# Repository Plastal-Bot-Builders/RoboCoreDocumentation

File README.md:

# RoboCore

RoboCore is a classroom robot kit and coding platform, designed and built in Zambia by **Plastal-Bot Builders** (Lusaka). It has four parts:
- an **ESP32-S3 controller board**;
- a **3D-printed robot** with a parallel lift and a geared gripper;
- a **retail box** with a quick-start guide;
- the **RoboCore IDE**, where students code the robot with blocks or C++.

This repository holds the design sources for all of it: the PCBs, the mechanical design, the software design and the brand. Pitch decks, grant applications and community posts live elsewhere.

<table>
  <tr>
    <td width="50%"></td>
    <td width="50%"></td>
  </tr>
  <tr>
    <td align="center"><b>The robot</b> (V2, Fusion 360)</td>
    <td align="center"><b>The controller board</b> (V2, KiCad 9)</td>
  </tr>
</table>

---

## The controller board (V2)

An XRP-style robot controller on a 68 × 60 mm, 4-layer board. Everything a classroom robot needs is on one board, and it charges and programs over one USB-C cable.

| | |
|---|---|
| **Brain** | ESP32-S3-WROOM-1-N8R2: dual core, Wi-Fi and Bluetooth LE, 8 MB flash, 2 MB PSRAM. Programs over native USB, so no separate programmer is needed |
| **Motors** | 2 DC motors with encoders (DRV8411A dual H-bridge, limited to 1.0 A per motor). JST SH 6-pin, matching the SparkFun XRP motors |
| **Servos** | 4 servo ports on a 5.5 V supply (TPS61089 boost, about 2.5–3 A continuous) |
| **Sensors** | Ultrasonic port (4-pin), 3-channel line-sensor port (5-pin, analog), Qwiic I2C, and an LSM6DSOX 6-axis motion sensor on board |
| **Power** | One Li-ion cell, or several in parallel (3.0–4.2 V), on an XT30 plug. Protected against a reversed or over-voltage pack. USB-C charging at 1 A (MCP73871) and a steady 3.3 V from a buck-boost converter |
| **On board** | RGB LED, buzzer, RESET, BOOT and USER buttons, charge and power LEDs, two 14-pin expansion headers |

<table>
  <tr>
    <td width="50%"></td>
    <td width="50%"></td>
  </tr>
  <tr>
    <td align="center">Top: every port labelled on the silkscreen</td>
    <td align="center">Underside: pin names and the "Designed in Zambia" artwork</td>
  </tr>
  <tr>
    <td></td>
    <td></td>
  </tr>
  <tr>
    <td align="center">The ESP32-S3 module, buttons and IMU</td>
    <td align="center">The connector edge: ultrasonic, battery, USB-C, line sensor, power switch</td>
  </tr>
</table>

- **Design files:** `hardware/controller_v2/`. Open `RoboCore_V2.kicad_pro` in KiCad 9.
- **Renders:** studio renders made in Blender are in `hardware/controller_v2/renders/`, full size and 1600 px, with transparent and white backgrounds. Each shot has a map of where every part sits in the image, for pinouts and highlights in the IDE or on the website. See [its README](hardware/controller_v2/renders/README.md).
- **Before connecting anything:** the sensor headers are not keyed, so a cable can go on backwards. Read [the wrong-plug check](docs/RoboCore_V2_wrong_plug_check.md). Known issues and bring-up findings are kept in [the errata list](docs/RoboCore_V2_errata.md).
- **Sensor boards:** our own 3-channel line sensor and ultrasonic boards are designed in `hardware/sensors/`. For now the robot uses bought-in modules.

## The robot

The current robot (V3, the V-wheel version): an open printed frame with Warren-truss sides, two encoder motors with 56 mm wheels, four V-wheels in wheel wells, a parallel four-bar lift on one MG90S servo (the gripper stays level from the floor to +40 degrees) and a geared gripper on a second servo. The RoboCore V2 controller sits between the side frames, three 18650 cells lie in a printed cradle, the sonar sits in a housing at the front, and a cream rear deck carries an 8 mm Technic/M4 hole grid. 154 x 286 x 111 mm with the lift level, about 620 g; every part prints flat without supports. The V3 model lives in Fusion 360 (document "RoboCore V3 Robot"); the files below are the earlier V2 robot, kept for reference.

- **Model:** `mechanical/robot_v2/RoboCore_V2_Robot.f3d` (Fusion 360) and `.step` (any CAD program).
- **Generator:** the model is built by a Python generator through the Fusion API (`mechanical/robot_v2/fusion/`). [Its README](mechanical/robot_v2/README.md) explains the parameters, the fasteners and the checks: clashes, overhangs, antenna clearance and caster load.
- **Print files:** `mechanical/robot_v2/print/`, already in print orientation. Every part prints without supports on a 180 mm bed.
- **Cardboard version:** a low-cost cardboard chassis template is in `mechanical/robot_v2/cardboard/`.

## The box

<table>
  <tr>
    <td width="50%"></td>
    <td width="50%"></td>
  </tr>
</table>

A printed mailer box, XRP-style, with the quick-start guide printed inside the lid and an insert with a pocket traced from the robot (lift lowered, jaws on the floor) plus a strip for the cable, screws and card. Outer 303 x 213 x 91 mm. The print-ready 1:1 PDFs are in `mechanical/robot_v2/packaging/out_v3/` (generator `make_box_v3.py`; the V2 box is in `out/`).

## Software

- **RoboCore IDE design** (`software/ide_design/`): the screens of the RoboCore IDE, built in Figma by a plugin. It covers block coding (Google Blockly) and C++ (Monaco), a hardware-first block catalogue, and a behaviour spec. The app itself is developed in its own repository, [robocore-ide](https://github.com/Plastal-Bot-Builders/robocore-ide).
- **System architecture** (`software/architecture/`): UML and C4 diagrams of the whole platform, also generated into Figma.
- **Firmware** (`software/firmware/motion/`): an arm-aware braking limiter in C, with tests.

## Brand

<table>
  <tr>
    <td width="33%"></td>
    <td width="33%"></td>
    <td width="33%"></td>
  </tr>
</table>

Event branding is in `design/event_branding/`: roll-up, pop-up, banner, A5 flyer, A4 tri-fold and the brand kit, built in Figma by a plugin. The topographic backgrounds are drawn from Copperbelt elevation data.

---

## Repository layout

```
hardware/          PCB design (KiCad 9)
  controller_v2/     RoboCore V2 controller: project files, libraries (lib/), PCBWay and JLCPCB order
                     packages (fab/), generator, check, costing and Blender render scripts (tools/),
                     silkscreen artwork sources (technicalreference/), studio renders (renders/)
  sensors/           Line sensor (3-channel) and ultrasonic carrier boards for V2
  controller_v1/     RoboCore V1 (ESP32-C3) controller with its fab package and review scripts
  libraries/         Shared symbol and footprint libraries used by V1
  datasheets/        Component datasheets
mechanical/        Mechanical design
  robot_v2/          The Fusion 360 robot: model, Python generator (fusion/), print files (print/),
                     component STEP exports (export/), mailer box (packaging/), cardboard version
                     (cardboard/), vendor models (vendor/), renders
  board_step/        STEP models of the boards, for mechanical integration
  reference/         Motor and XRP reference pictures and models
  chassis_v1_spec/   Specification and script of the V1 chassis
software/          Software
  ide_design/        RoboCore IDE screens (Figma plugin), app icon, block catalogue, behaviour spec
  architecture/      UML + C4 system architecture (Figma plugin)
  firmware/motion/   Arm-aware braking limiter (C, with tests)
design/            Brand
  event_branding/    Roll-up, banner, flyer, tri-fold and brand kit (Figma plugin), topographic maps
docs/              Specification, costing and sourcing, component lists and supplier quote requests,
                   wrong-plug check and errata, schematic PDFs, part photos, A4 technical-reference
                   posters, progress renders, hand-off notes, PCBWay sponsorship request
tools/             sync_from_sources.sh: copies the working sources into this repo
```

## Opening the designs

- **PCB:** open `hardware/controller_v2/RoboCore_V2.kicad_pro` in KiCad 9. Project libraries resolve through `${KIPRJMOD}/lib`; the V1 project's symbol table points at `../libraries`.
- **Robot:** `mechanical/robot_v2/RoboCore_V2_Robot.f3d` opens in Fusion 360; the STEP beside it opens anywhere.
- **Box:** `mechanical/robot_v2/packaging/README.md`. The print files are 1:1 PDFs.
- **Board renders:** `hardware/controller_v2/tools/blender/render_board.sh` re-renders them in Blender 5.1, from the KiCad model.
- **Figma plugins:** the READMEs in `software/ide_design/`, `software/architecture/` and `design/event_branding/` explain how to load and run each plugin.

## Status (2026-10-23)

- **Controller V2:** two assembled prototypes are paid for at PCBWay (order YU1827457, 14 October) and expected to ship around 11 November. Bring-up findings will go into [the errata list](docs/RoboCore_V2_errata.md).
- **Robot:** rev 6. The model and STEP here are Fusion v33.
- **Sensor boards:** designed, not yet ordered. The robot uses bought-in modules for now.
- **IDE:** in development in [robocore-ide](https://github.com/Plastal-Bot-Builders/robocore-ide).
- **Parts:** the component list and supplier quote request for two robots are in `docs/`.

## Keeping this repo up to date

The design work happens in working folders outside this repo. Copy it in, then commit:

```bash
tools/sync_from_sources.sh           # list what changed
tools/sync_from_sources.sh --apply   # copy it in
```

The script lists every source folder it copies. On a slow connection, push large changes in several small commits.

## Licence

MIT, see `LICENSE`. Vendor models under `mechanical/robot_v2/vendor/` keep their own licences, noted in each folder's `SOURCE.txt`.

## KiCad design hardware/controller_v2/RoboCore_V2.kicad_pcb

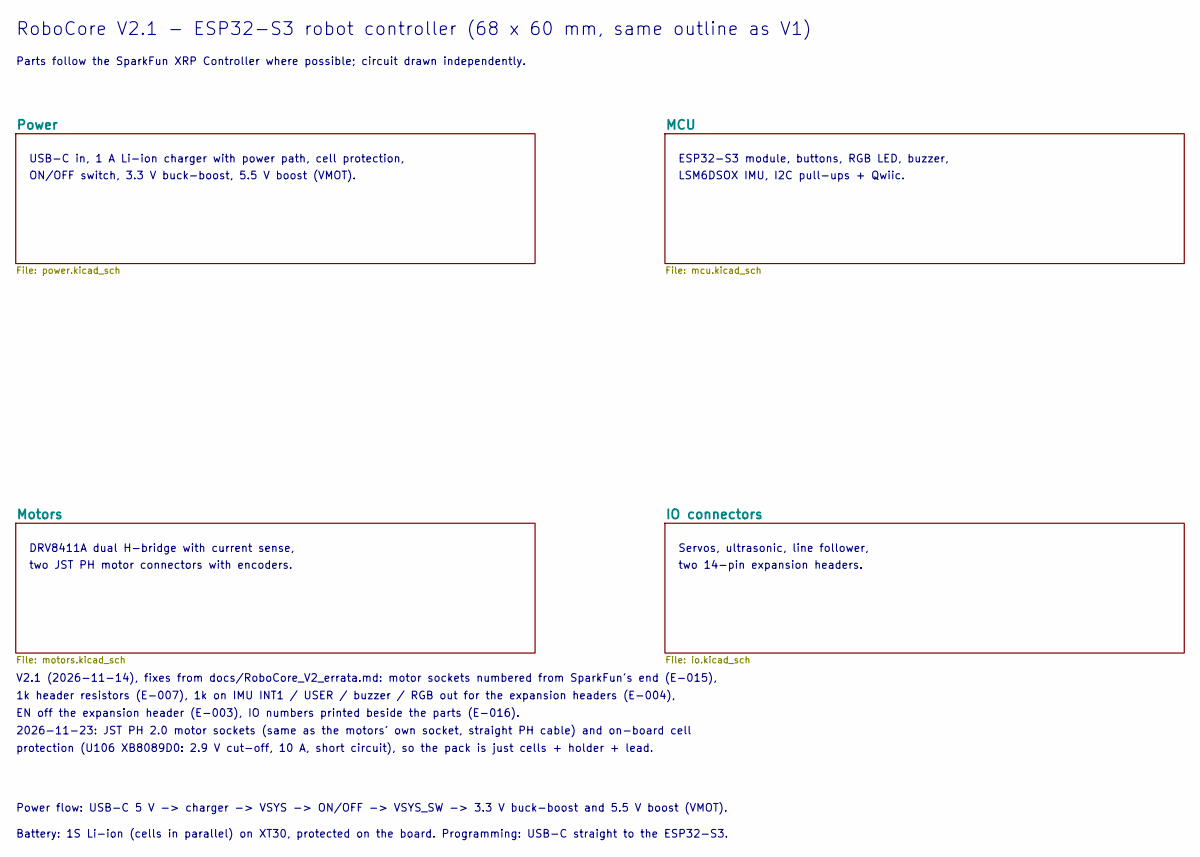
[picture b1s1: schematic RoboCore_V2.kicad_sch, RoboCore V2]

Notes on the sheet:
USB-C in, 1 A Li-ion charger with power path, cell protection,
ON/OFF switch, 3.3 V buck-boost, 5.5 V boost (VMOT).
ESP32-S3 module, buttons, RGB LED, buzzer,
LSM6DSOX IMU, I2C pull-ups + Qwiic.
DRV8411A dual H-bridge with current sense,
two JST PH motor connectors with encoders.
Servos, ultrasonic, line follower,
two 14-pin expansion headers.
RoboCore V2.1 - ESP32-S3 robot controller (68 x 60 mm, same outline as V1)
V2.1 (2026-11-14), fixes from docs/RoboCore_V2_errata.md: motor sockets numbered from SparkFun's end (E-015),
1k header resistors (E-007), 1k on IMU INT1 / USER / buzzer / RGB out for the expansion headers (E-004),
EN off the expansion header (E-003), IO numbers printed beside the parts (E-016).
2026-11-23: JST PH 2.0 motor sockets (same as the motors' own socket, straight PH cable) and on-board cell
protection (U106 XB8089D0: 2.9 V cut-off, 10 A, short circuit), so the pack is just cells + holder + lead.
Parts follow the SparkFun XRP Controller where possible; circuit drawn independently.
Power flow: USB-C 5 V -> charger -> VSYS -> ON/OFF -> VSYS_SW -> 3.3 V buck-boost and 5.5 V boost (VMOT).
Battery: 1S Li-ion (cells in parallel) on XT30, protected on the board. Programming: USB-C straight to the ESP32-S3.

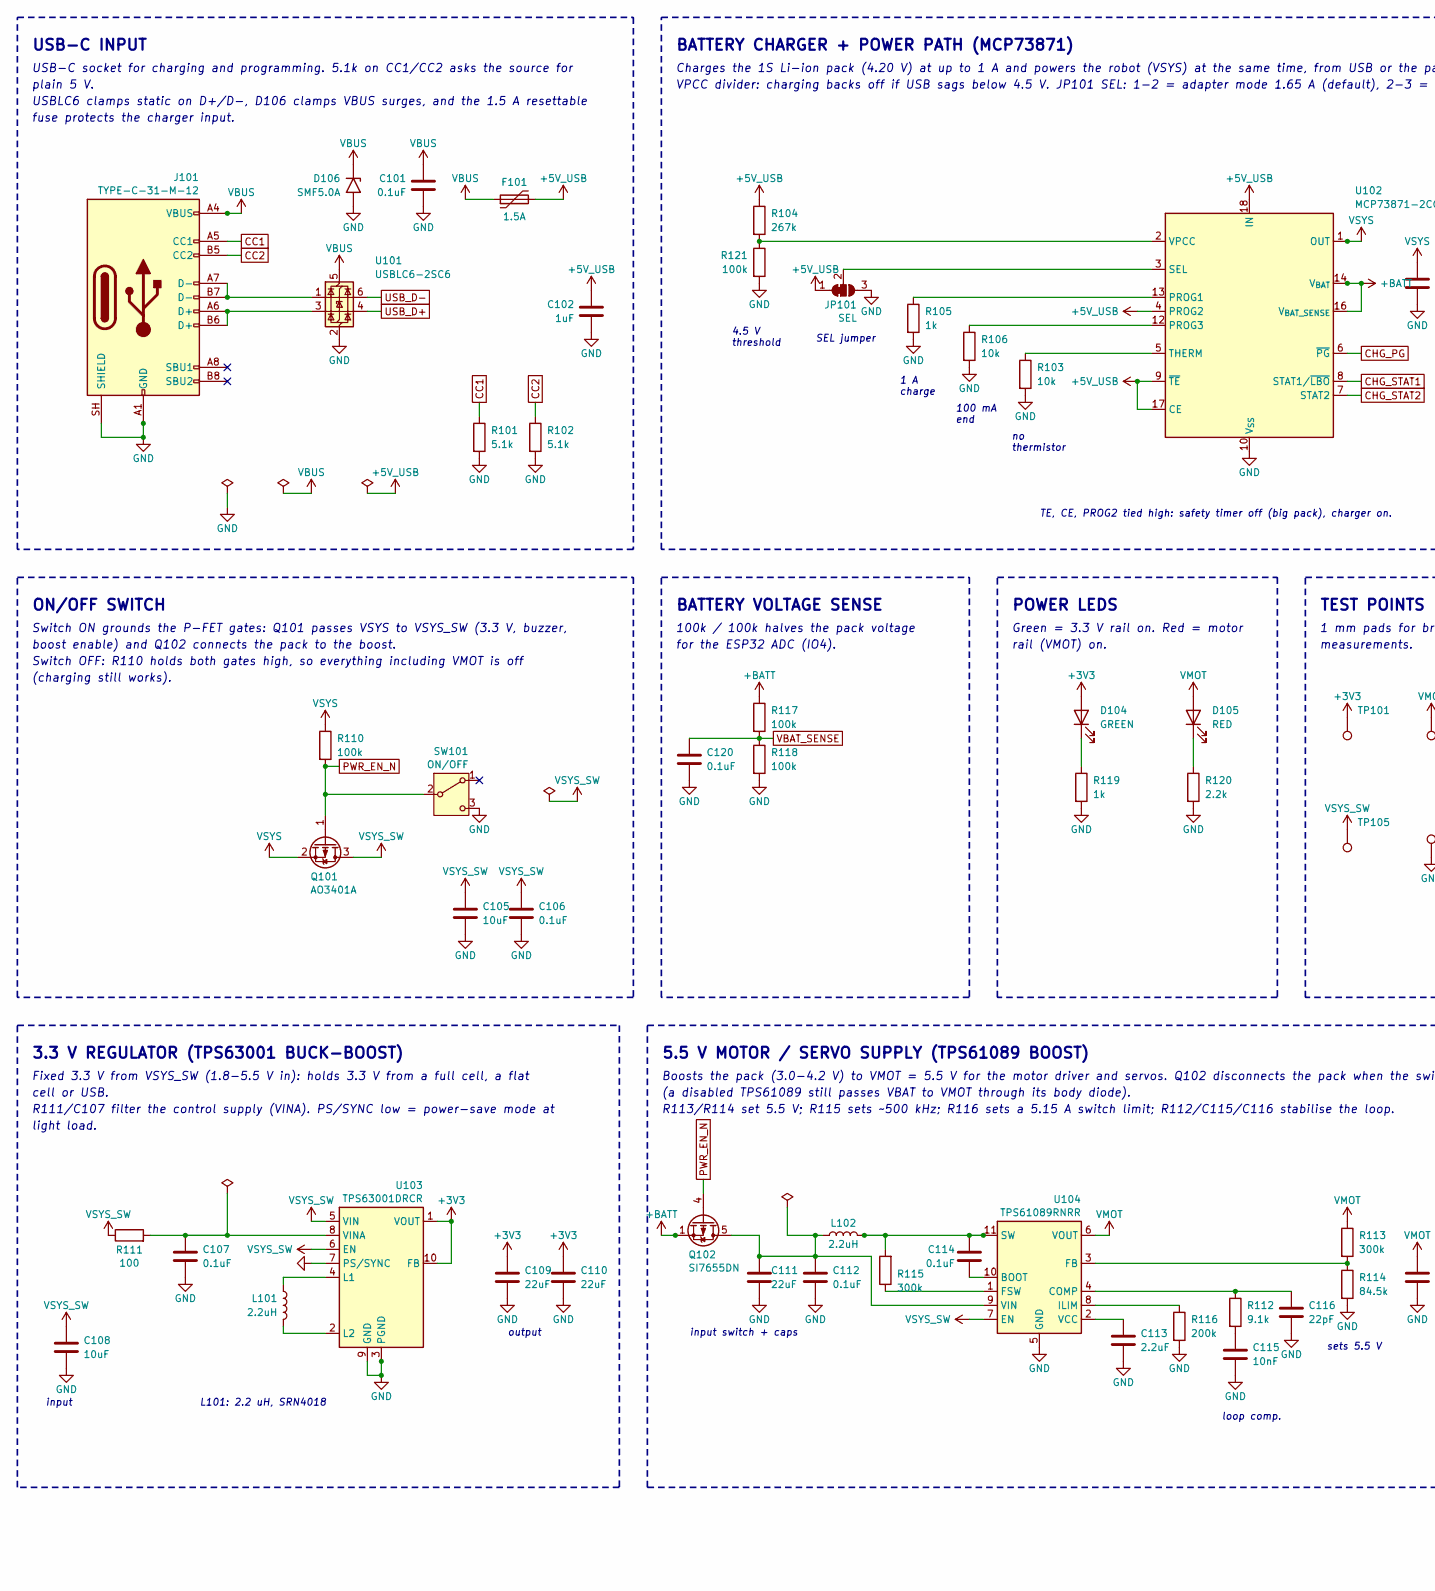
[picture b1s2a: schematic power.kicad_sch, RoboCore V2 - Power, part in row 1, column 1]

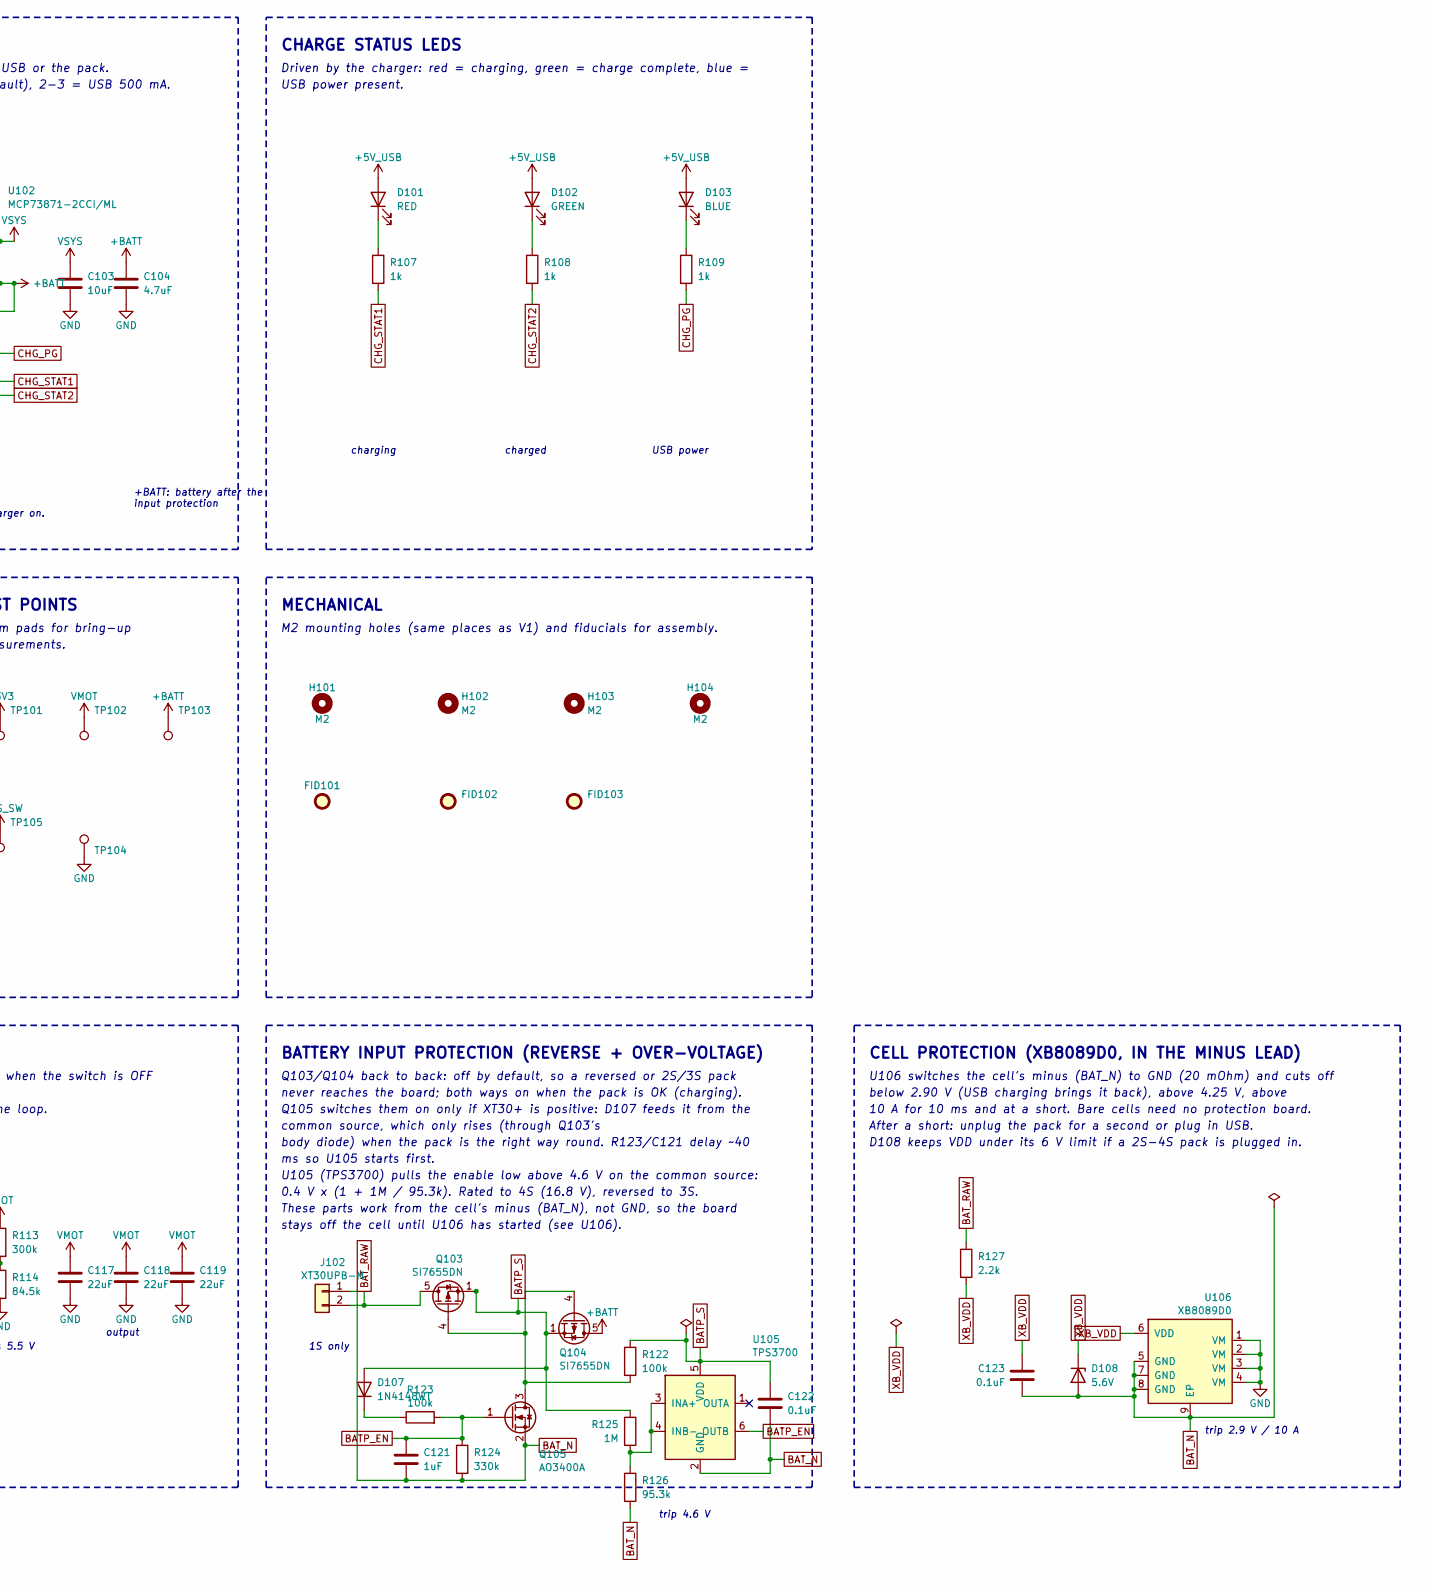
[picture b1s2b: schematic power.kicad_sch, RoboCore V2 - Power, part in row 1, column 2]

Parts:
C101, C106, C107, C112, C114, C120, C122, C123: 0.1uF; C_0402_1005Metric; LCSC C960916
C102: 1uF; C_0603_1608Metric; LCSC C5673
C103: 10uF; C_0603_1608Metric; LCSC C92487
C104: 4.7uF; C_0805_2012Metric; LCSC C1779
C105, C108: 10uF; C_0805_2012Metric; LCSC C1713
C109, C110: 22uF; C_0805_2012Metric; LCSC C45783
C111, C117, C118, C119: 22uF; C_1206_3216Metric; LCSC C12891
C113: 2.2uF; C_0603_1608Metric; LCSC C23630
C115: 10nF; C_0402_1005Metric; LCSC C15195
C116: 22pF; C_0402_1005Metric; LCSC C70464
C121: 1uF; C_0402_1005Metric; LCSC C16193167
D101, D105: RED; LED_0603_1608Metric; LCSC C125099
D102, D104: GREEN; LED_0603_1608Metric; LCSC C125098
D103: BLUE; LED_0603_1608Metric; LCSC C99290
D106: SMF5.0A; D_SMF; LCSC C151296
D107: 1N4148WT; D_SOD-523; LCSC C232841
D108: 5.6V; D_SOD-523; LCSC C516598
F101: 1.5A; Fuse_1812_4532Metric; LCSC C78695
FID101, FID102, FID103: Fiducial; Fiducial_1mm_Mask2mm
H101, H102, H103, H104: M2; MountingHole_2.2mm_M2
J101: TYPE-C-31-M-12; USB_C_Receptacle_HRO_TYPE-C-31-M-12; LCSC C165948
J102: XT30UPB-M; AMASS_XT30UPB-M_1x02_P5.0mm_Vertical; LCSC C428721
JP101: SEL; SolderJumper-3_P1.3mm_Bridged12_RoundedPad1.0x1.5mm
L101: 2.2uH; L_Bourns-SRN4018; LCSC C913207
L102: 2.2uH; L_Bourns_SRP5030CA; LCSC C2046809
Q101: AO3401A; SOT-23; LCSC C15127
Q102, Q103, Q104: SI7655DN; Vishay_PowerPAK_1212-8_Single; LCSC C727830
Q105: AO3400A; SOT-23; LCSC C20917
R101, R102: 5.1k; R_0402_1005Metric; LCSC C25905
R103, R106: 10k; R_0402_1005Metric; LCSC C25744
R104: 267k; R_0402_1005Metric; LCSC C270622
R105, R107, R108, R109, R119: 1k; R_0402_1005Metric; LCSC C106235
R110, R117, R118, R121, R122, R123: 100k; R_0402_1005Metric; LCSC C25741
R111: 100; R_0402_1005Metric; LCSC C106232
R112: 9.1k; R_0402_1005Metric; LCSC C25926
R113, R115: 300k; R_0402_1005Metric; LCSC C25774
R114: 84.5k; R_0402_1005Metric; LCSC C26988
R116: 200k; R_0402_1005Metric; LCSC C25764
R120, R127: 2.2k; R_0402_1005Metric; LCSC C25879
R124: 330k; R_0402_1005Metric; LCSC C25778
R125: 1M; R_0402_1005Metric; LCSC C26083
R126: 95.3k; R_0402_1005Metric; LCSC C26990
SW101: ON/OFF; SW_SPDT_CK_JS102011SAQN; LCSC C221660
TP101: +3V3; TestPoint_Pad_D1.0mm
TP102: VMOT; TestPoint_Pad_D1.0mm
TP103: +BATT; TestPoint_Pad_D1.0mm
TP104: GND; TestPoint_Pad_D1.0mm
TP105: VSYS_SW; TestPoint_Pad_D1.0mm
U101: USBLC6-2SC6; SOT-23-6; LCSC C7519
U102: MCP73871-2CCI/ML; QFN-20-1EP_4x4mm_P0.5mm_EP2.5x2.5mm_ThermalVias; LCSC C5121473
U103: TPS63001DRCR; Texas_DRC0010J_ThermalVias; LCSC C28060
U104: TPS61089RNRR; Texas_VQFN-RNR0011A-11; LCSC C165129
U105: TPS3700; TSOT-23-6; LCSC C33002
U106: XB8089D0; SOIC-8-1EP_3.9x4.9mm_P1.27mm_EP2.41x3.3mm; LCSC C2760005

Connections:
+3V3: C109.1, C110.1, D104.2 (A), TP101.1, U103.1 (VOUT), U103.10 (FB); also elsewhere on the board
+5V_USB: C102.1, D101.2 (A), D102.2 (A), D103.2 (A), F101.2, JP101.1 (A), R104.1, U102.4 (PROG2), U102.9 (~TE), U102.17 (CE), U102.18 (IN), U102.19 (IN)
+BATT: C104.1, Q102.1 (S), Q102.2 (S), Q102.3 (S), Q104.5 (D), R117.1, TP103.1, U102.14 (V_{BAT}), U102.15 (V_{BAT}), U102.16 (V_{BAT_SENSE})
BATP_EN: C121.1, Q105.1 (G), R123.2, R124.1, U105.6 (OUTB)
BATP_S: C122.1, D107.2 (A), Q103.1 (S), Q103.2 (S), Q103.3 (S), Q104.1 (S), Q104.2 (S), Q104.3 (S), R122.1, R125.1, U105.5 (VDD)
BAT_N: C121.2, C122.2, C123.2, D108.2 (A), J102.1, Q105.2 (S), R124.2, R126.2, U105.2 (GND), U106.5 (GND), U106.7 (GND), U106.8 (GND), U106.9 (EP)
BAT_RAW: J102.2, Q103.5 (D), R127.1
CC1: J101.A5 (CC1), R101.1
CC2: J101.B5 (CC2), R102.1
CHG_PG: R109.2, U102.6 (~PG)
CHG_STAT1: R107.2, U102.8 (STAT1/~LBO)
CHG_STAT2: R108.2, U102.7 (STAT2)
GND: C101.2, C102.2, C103.2, C104.2, C105.2, C106.2, C107.2, C108.2, C109.2, C110.2, C111.2, C112.2, C113.2, C115.2, C116.2, C117.2, C118.2, C119.2, C120.2, D106.2 (A2), J101.A1 (GND), J101.A12 (GND), J101.B1 (GND), J101.B12 (GND), J101.SH (SHIELD), JP101.3 (B), R101.2, R102.2, R103.2, R105.2, R106.2, R114.2, R116.2, R118.2, R119.2, R120.2, R121.2, SW101.3 (C), TP104.1, U101.2 (GND), U102.10 (V_{SS}), U102.11 (V_{SS}), U102.21 (V_{SS}), U103.3 (PGND), U103.7 (PS/SYNC), U103.9 (GND), U103.11 (PGND), U104.5 (GND), U106.1 (VM), U106.2 (VM), U106.3 (VM), U106.4 (VM); also elsewhere on the board
unnamed: C115.1, R112.2
unnamed: D101.1 (K), R107.1
unnamed: D102.1 (K), R108.1
unnamed: D103.1 (K), R109.1
unnamed: D104.1 (K), R119.1
unnamed: D105.1 (K), R120.1
unnamed: D107.1 (K), R123.1
unnamed: J101.A6 (D+), J101.B6 (D+), U101.3 (I/O2)
unnamed: J101.A7 (D-), J101.B7 (D-), U101.1 (I/O1)
unnamed: JP101.2 (C), U102.3 (SEL)
unnamed: C111.1, C112.1, L102.1, Q102.5 (D), U104.9 (VIN)
unnamed: Q103.4 (G), Q104.4 (G), Q105.3 (D), R122.2
unnamed: R105.1, U102.13 (PROG1)
unnamed: R106.1, U102.12 (PROG3)
unnamed: R103.1, U102.5 (THERM)
unnamed: R104.2, R121.1, U102.2 (VPCC)
unnamed: L101.1, U103.4 (L1)
unnamed: L101.2, U103.2 (L2)
unnamed: C107.1, R111.2, U103.8 (VINA)
unnamed: C114.1, U104.10 (BOOT)
unnamed: C116.1, R112.1, U104.4 (COMP)
unnamed: R113.2, R114.1, U104.3 (FB)
unnamed: R115.1, U104.1 (FSW)
unnamed: R116.1, U104.8 (ILIM)
unnamed: C114.2, L102.2, R115.2, U104.11 (SW)
unnamed: C113.1, U104.2 (VCC)
unnamed: R125.2, R126.1, U105.3 (INA+), U105.4 (INB-)
PWR_EN_N: Q101.1 (G), Q102.4 (G), R110.2, SW101.2 (B)
USB_D+: U101.4 (I/O2); also elsewhere on the board
USB_D-: U101.6 (I/O1); also elsewhere on the board
VBAT_SENSE: C120.1, R117.2, R118.1; also elsewhere on the board
VBUS: C101.1, D106.1 (A1), F101.1, J101.A4 (VBUS), J101.A9 (VBUS), J101.B4 (VBUS), J101.B9 (VBUS), U101.5 (VBUS)
VMOT: C117.1, C118.1, C119.1, D105.2 (A), R113.1, TP102.1, U104.6 (VOUT); also elsewhere on the board
VSYS: C103.1, Q101.2 (S), R110.1, U102.1 (OUT), U102.20 (OUT)
VSYS_SW: C105.1, C106.1, C108.1, Q101.3 (D), R111.1, TP105.1, U103.5 (VIN), U103.6 (EN), U104.7 (EN); also elsewhere on the board
XB_VDD: C123.1, D108.1 (K), R127.2, U106.6 (VDD)

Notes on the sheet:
USB-C INPUT
USB-C socket for charging and programming. 5.1k on CC1/CC2 asks the source for
plain 5 V.
USBLC6 clamps static on D+/D-, D106 clamps VBUS surges, and the 1.5 A resettable
fuse protects the charger input.
BATTERY CHARGER + POWER PATH (MCP73871)
Charges the 1S Li-ion pack (4.20 V) at up to 1 A and powers the robot (VSYS) at the same time, from USB or the pack.
VPCC divider: charging backs off if USB sags below 4.5 V. JP101 SEL: 1-2 = adapter mode 1.65 A (default), 2-3 = USB 500 mA.
4.5 V
threshold
SEL jumper
1 A
charge
100 mA
end
thermistor
TE, CE, PROG2 tied high: safety timer off (big pack), charger on.
+BATT: battery after the
input protection
CHARGE STATUS LEDS
Driven by the charger: red = charging, green = charge complete, blue =
USB power present.
charging
charged
USB power
ON/OFF SWITCH
Switch ON grounds the P-FET gates: Q101 passes VSYS to VSYS_SW (3.3 V, buzzer,
boost enable) and Q102 connects the pack to the boost.
Switch OFF: R110 holds both gates high, so everything including VMOT is off
(charging still works).
BATTERY VOLTAGE SENSE
100k / 100k halves the pack voltage
for the ESP32 ADC (IO4).
POWER LEDS
Green = 3.3 V rail on. Red = motor
rail (VMOT) on.
TEST POINTS
1 mm pads for bring-up
measurements.
MECHANICAL

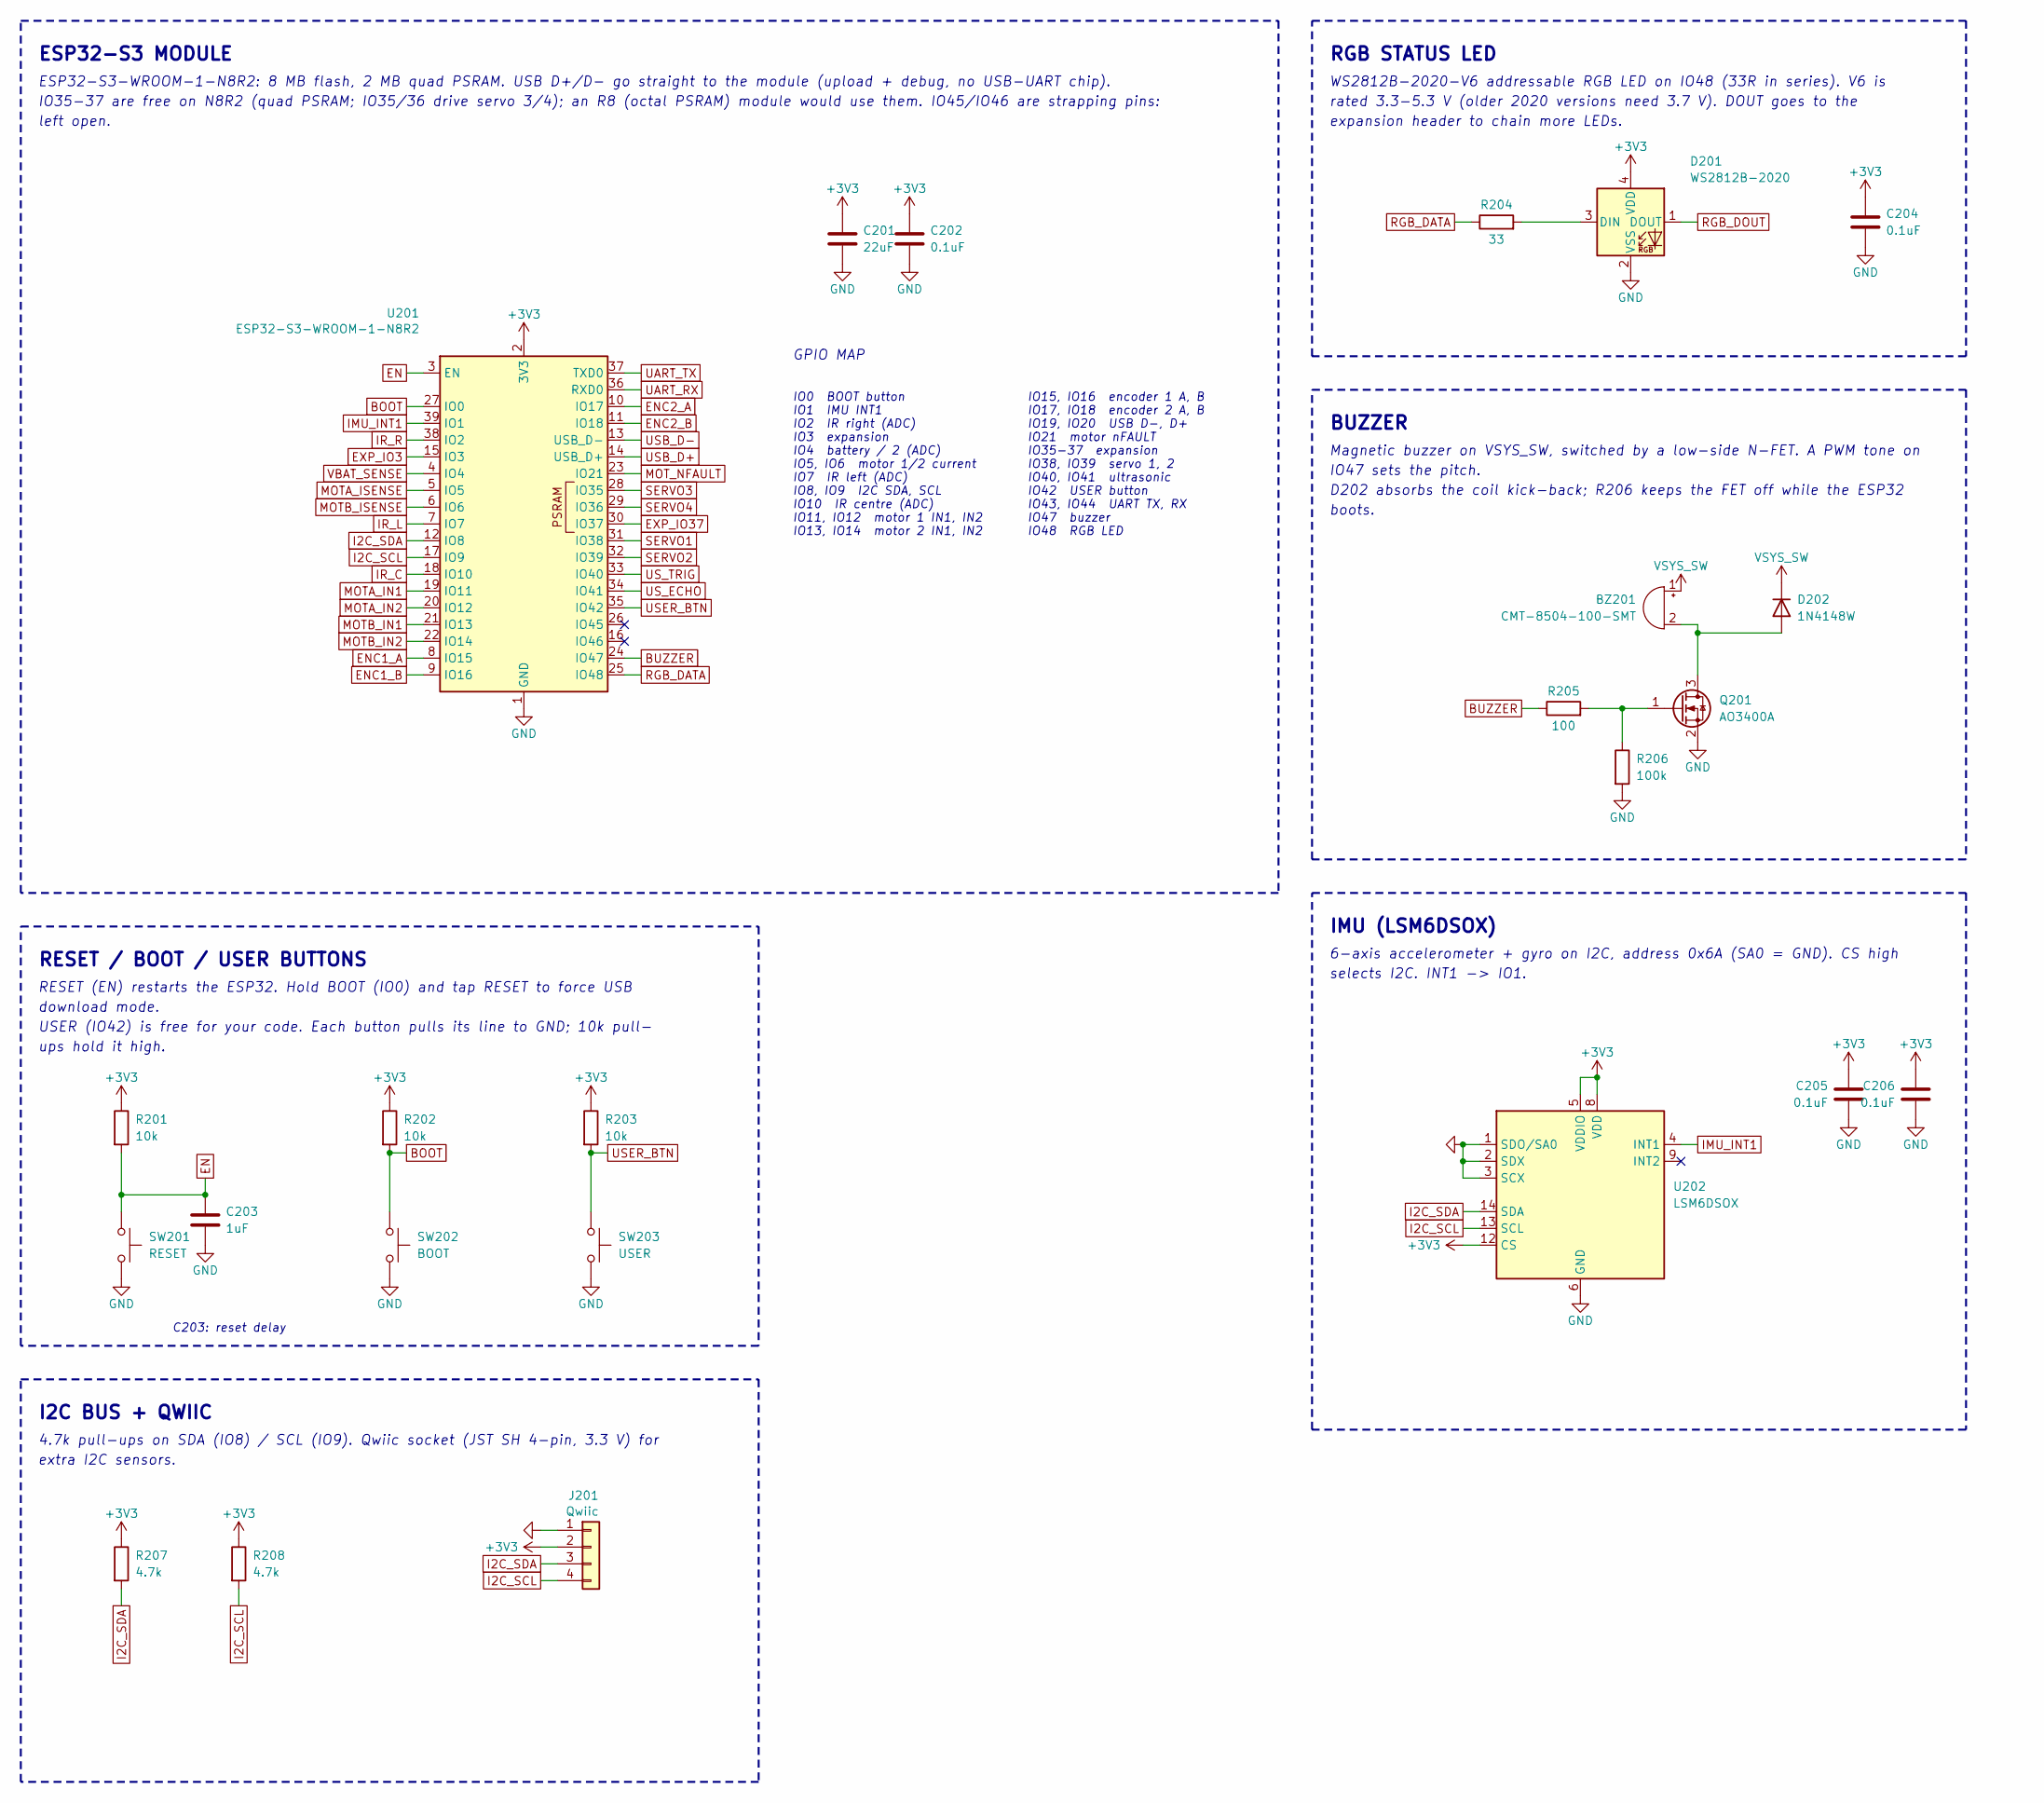
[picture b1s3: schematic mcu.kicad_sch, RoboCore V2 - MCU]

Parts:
BZ201: CMT-8504-100-SMT; MagneticBuzzer_CUI_CMT-8504-100-SMT; LCSC C22359707
C201: 22uF; C_0805_2012Metric; LCSC C45783
C202, C204, C205, C206: 0.1uF; C_0402_1005Metric; LCSC C960916
C203: 1uF; C_0402_1005Metric; LCSC C16193167
D201: WS2812B-2020; LED_WS2812B-2020_PLCC4_2.0x2.0mm; LCSC C52917434
D202: 1N4148W; D_SOD-123; LCSC C83528
J201: Qwiic; JST_SH_BM04B-SRSS-TB_1x04-1MP_P1.00mm_Vertical; LCSC C160390
Q201: AO3400A; SOT-23; LCSC C20917
R201, R202, R203: 10k; R_0402_1005Metric; LCSC C25744
R204: 33; R_0402_1005Metric; LCSC C138002
R205: 100; R_0402_1005Metric; LCSC C106232
R206: 100k; R_0402_1005Metric; LCSC C25741
R207, R208: 4.7k; R_0402_1005Metric; LCSC C25900
SW201: RESET; SW_SPST_SKQG_WithoutStem; LCSC C116647
SW202: BOOT; SW_SPST_SKQG_WithoutStem; LCSC C116647
SW203: USER; SW_SPST_SKQG_WithoutStem; LCSC C116647
U201: ESP32-S3-WROOM-1-N8R2; ESP32-S3-WROOM-1; LCSC C2913204
U202: LSM6DSOX; LGA-14_3x2.5mm_P0.5mm_LayoutBorder3x4y; LCSC C481766

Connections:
+3V3: C201.1, C202.1, C204.1, C205.1, C206.1, D201.4 (VDD), J201.2, R201.1, R202.1, R203.1, R207.1, R208.1, U201.2 (3V3), U202.5 (VDDIO), U202.8 (VDD), U202.12 (CS); also elsewhere on the board
BOOT: R202.2, SW202.1, U201.27 (IO0)
BUZZER: R205.1, U201.24 (IO47); also elsewhere on the board
EN: C203.1, R201.2, SW201.1, U201.3 (EN)
ENC1_A: U201.8 (IO15); also elsewhere on the board
ENC1_B: U201.9 (IO16); also elsewhere on the board
ENC2_A: U201.10 (IO17); also elsewhere on the board
ENC2_B: U201.11 (IO18); also elsewhere on the board
EXP_IO3: U201.15 (IO3); also elsewhere on the board
EXP_IO37: U201.30 (IO37); also elsewhere on the board
GND: C201.2, C202.2, C203.2, C204.2, C205.2, C206.2, D201.2 (VSS), J201.1, Q201.2 (S), R206.2, SW201.2, SW202.2, SW203.2, U201.1 (GND), U201.40 (GND), U201.41 (GND), U202.1 (SDO/SA0), U202.2 (SDX), U202.3 (SCX), U202.6 (GND), U202.7 (GND); also elsewhere on the board
I2C_SCL: J201.4, R208.2, U201.17 (IO9), U202.13 (SCL); also elsewhere on the board
I2C_SDA: J201.3, R207.2, U201.12 (IO8), U202.14 (SDA); also elsewhere on the board
IMU_INT1: U201.39 (IO1), U202.4 (INT1); also elsewhere on the board
IR_C: U201.18 (IO10); also elsewhere on the board
IR_L: U201.7 (IO7); also elsewhere on the board
IR_R: U201.38 (IO2); also elsewhere on the board
MOTA_IN1: U201.19 (IO11); also elsewhere on the board
MOTA_IN2: U201.20 (IO12); also elsewhere on the board
MOTA_ISENSE: U201.5 (IO5); also elsewhere on the board
MOTB_IN1: U201.21 (IO13); also elsewhere on the board
MOTB_IN2: U201.22 (IO14); also elsewhere on the board
MOTB_ISENSE: U201.6 (IO6); also elsewhere on the board
MOT_NFAULT: U201.23 (IO21); also elsewhere on the board
unnamed: BZ201.2 (-), D202.2 (A), Q201.3 (D)
unnamed: D201.3 (DIN), R204.2
unnamed: Q201.1 (G), R205.2, R206.1
RGB_DATA: R204.1, U201.25 (IO48)
RGB_DOUT: D201.1 (DOUT); also elsewhere on the board
SERVO1: U201.31 (IO38); also elsewhere on the board
SERVO2: U201.32 (IO39); also elsewhere on the board
SERVO3: U201.28 (IO35); also elsewhere on the board
SERVO4: U201.29 (IO36); also elsewhere on the board
UART_RX: U201.36 (RXD0); also elsewhere on the board
UART_TX: U201.37 (TXD0); also elsewhere on the board
USB_D+: U201.14 (USB_D+); also elsewhere on the board
USB_D-: U201.13 (USB_D-); also elsewhere on the board
USER_BTN: R203.2, SW203.1, U201.35 (IO42); also elsewhere on the board
US_ECHO: U201.34 (IO41); also elsewhere on the board
US_TRIG: U201.33 (IO40); also elsewhere on the board
VBAT_SENSE: U201.4 (IO4); also elsewhere on the board
VSYS_SW: BZ201.1 (+), D202.1 (K); also elsewhere on the board

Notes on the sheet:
ESP32-S3 MODULE
ESP32-S3-WROOM-1-N8R2: 8 MB flash, 2 MB quad PSRAM. USB D+/D- go straight to the module (upload + debug, no USB-UART chip).
IO35-37 are free on N8R2 (quad PSRAM; IO35/36 drive servo 3/4); an R8 (octal PSRAM) module would use them. IO45/IO46 are strapping pins:
left open.
GPIO MAP
IO0 BOOT button
IO1 IMU INT1
IO2 IR right (ADC)
IO3 expansion
IO4 battery / 2 (ADC)
IO5, IO6 motor 1/2 current
IO7 IR left (ADC)
IO8, IO9 I2C SDA, SCL
IO10 IR centre (ADC)
IO11, IO12 motor 1 IN1, IN2
IO13, IO14 motor 2 IN1, IN2
IO15, IO16 encoder 1 A, B
IO17, IO18 encoder 2 A, B
IO19, IO20 USB D-, D+
IO21 motor nFAULT
IO35-37 expansion
IO38, IO39 servo 1, 2
IO40, IO41 ultrasonic
IO42 USER button
IO43, IO44 UART TX, RX
IO47 buzzer
IO48 RGB LED
RESET / BOOT / USER BUTTONS
RESET (EN) restarts the ESP32. Hold BOOT (IO0) and tap RESET to force USB
download mode.
USER (IO42) is free for your code. Each button pulls its line to GND; 10k pull-
ups hold it high.
C203: reset delay
I2C BUS + QWIIC
4.7k pull-ups on SDA (IO8) / SCL (IO9). Qwiic socket (JST SH 4-pin, 3.3 V) for
extra I2C sensors.
RGB STATUS LED
WS2812B-2020-V6 addressable RGB LED on IO48 (33R in series). V6 is
rated 3.3-5.3 V (older 2020 versions need 3.7 V). DOUT goes to the
expansion header to chain more LEDs.

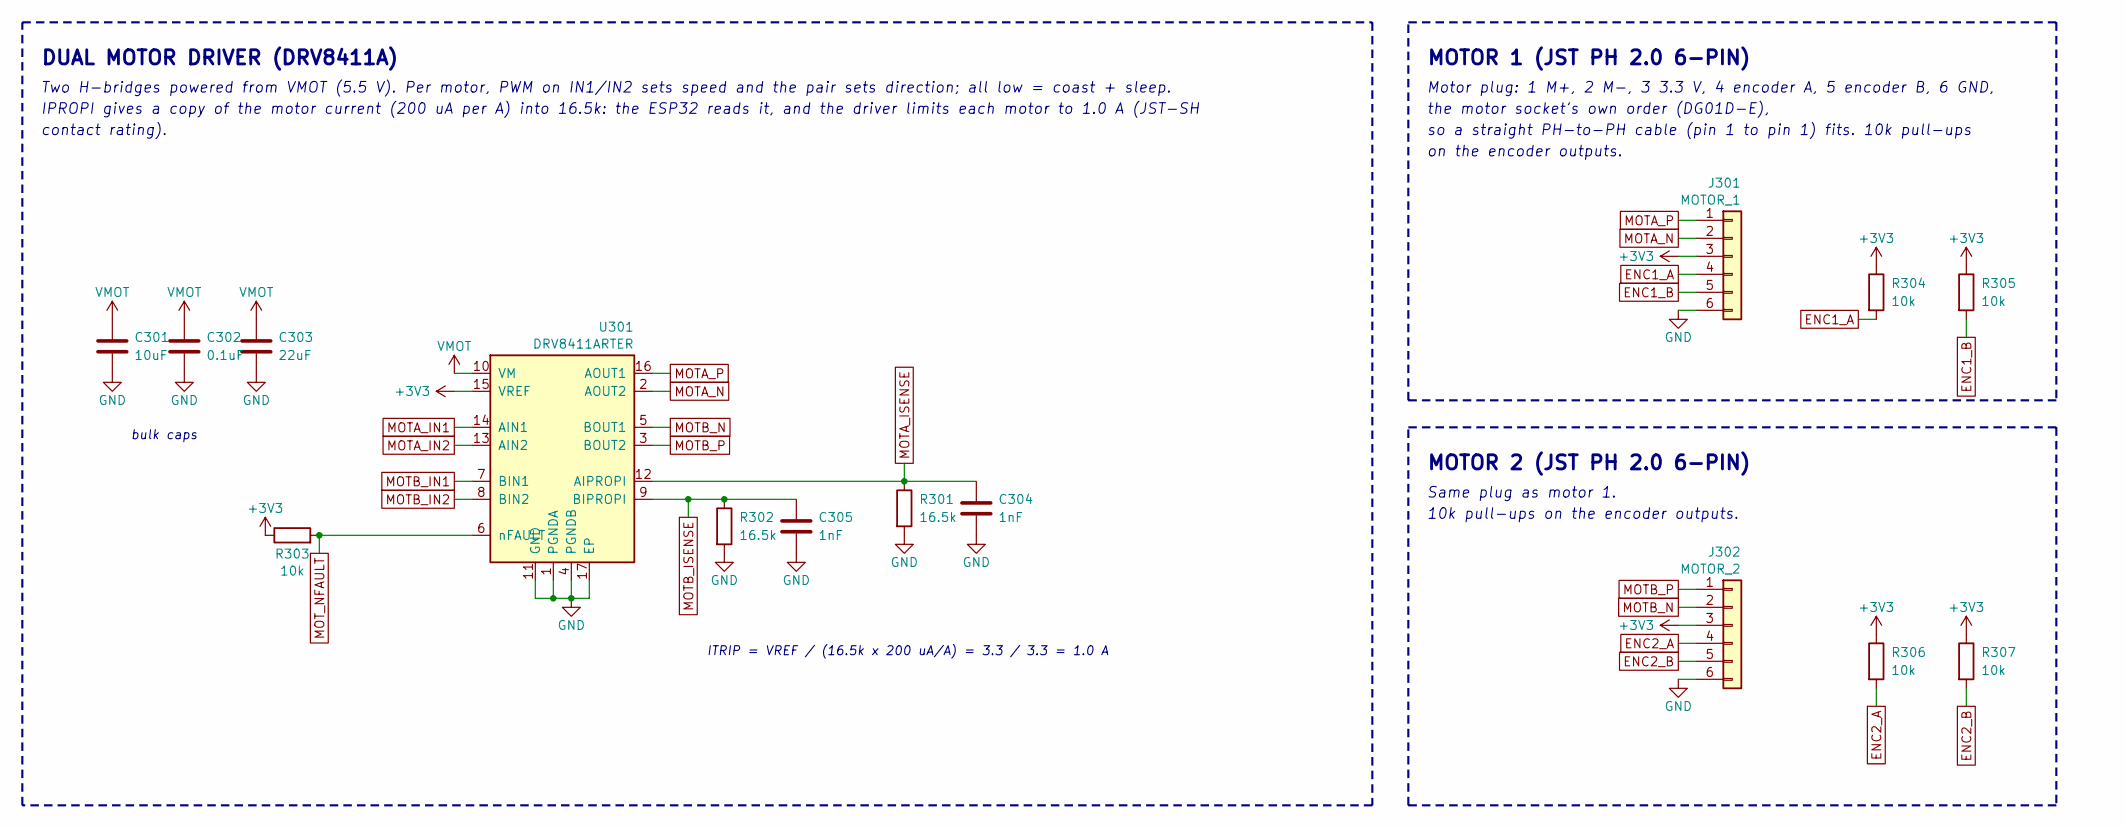
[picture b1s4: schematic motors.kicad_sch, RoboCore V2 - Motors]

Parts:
C301: 10uF; C_0805_2012Metric; LCSC C1713
C302: 0.1uF; C_0402_1005Metric; LCSC C960916
C303: 22uF; C_1206_3216Metric; LCSC C12891
C304, C305: 1nF; C_0402_1005Metric; LCSC C14442
J301: MOTOR_1; JST_PH_B6B-PH-K_1x06_P2.00mm_Vertical; LCSC C131342
J302: MOTOR_2; JST_PH_B6B-PH-K_1x06_P2.00mm_Vertical; LCSC C131342
R301, R302: 16.5k; R_0402_1005Metric; LCSC C25857
R303, R304, R305, R306, R307: 10k; R_0402_1005Metric; LCSC C25744
U301: DRV8411ARTER; WQFN-16-1EP_3x3mm_P0.5mm_EP1.68x1.68mm_ThermalVias; LCSC C18816315

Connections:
+3V3: J301.3, J302.3, R303.1, R304.1, R305.1, R306.1, R307.1, U301.15 (VREF); also elsewhere on the board
ENC1_A: J301.4, R304.2; also elsewhere on the board
ENC1_B: J301.5, R305.2; also elsewhere on the board
ENC2_A: J302.4, R306.2; also elsewhere on the board
ENC2_B: J302.5, R307.2; also elsewhere on the board
GND: C301.2, C302.2, C303.2, C304.2, C305.2, J301.6, J302.6, R301.2, R302.2, U301.1 (PGNDA), U301.4 (PGNDB), U301.11 (GND), U301.17 (EP); also elsewhere on the board
MOTA_IN1: U301.14 (AIN1); also elsewhere on the board
MOTA_IN2: U301.13 (AIN2); also elsewhere on the board
MOTA_ISENSE: C304.1, R301.1, U301.12 (AIPROPI); also elsewhere on the board
MOTA_N: J301.2, U301.2 (AOUT2)
MOTA_P: J301.1, U301.16 (AOUT1)
MOTB_IN1: U301.7 (BIN1); also elsewhere on the board
MOTB_IN2: U301.8 (BIN2); also elsewhere on the board
MOTB_ISENSE: C305.1, R302.1, U301.9 (BIPROPI); also elsewhere on the board
MOTB_N: J302.2, U301.5 (BOUT1)
MOTB_P: J302.1, U301.3 (BOUT2)
MOT_NFAULT: R303.2, U301.6 (nFAULT); also elsewhere on the board
VMOT: C301.1, C302.1, C303.1, U301.10 (VM); also elsewhere on the board

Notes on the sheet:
DUAL MOTOR DRIVER (DRV8411A)
Two H-bridges powered from VMOT (5.5 V). Per motor, PWM on IN1/IN2 sets speed and the pair sets direction; all low = coast + sleep.
IPROPI gives a copy of the motor current (200 uA per A) into 16.5k: the ESP32 reads it, and the driver limits each motor to 1.0 A (JST-SH
contact rating).
ITRIP = VREF / (16.5k x 200 uA/A) = 3.3 / 3.3 = 1.0 A
bulk caps
MOTOR 1 (JST PH 2.0 6-PIN)
Motor plug: 1 M+, 2 M-, 3 3.3 V, 4 encoder A, 5 encoder B, 6 GND,
the motor socket's own order (DG01D-E),
so a straight PH-to-PH cable (pin 1 to pin 1) fits. 10k pull-ups
on the encoder outputs.
MOTOR 2 (JST PH 2.0 6-PIN)
Same plug as motor 1.
10k pull-ups on the encoder outputs.
